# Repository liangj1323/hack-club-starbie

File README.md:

This is the repo for my hack club half life week one project for the Starbie PCB
It is an idea like a desk-pet Starboy, which you can shake, etc with it and it reacts
This is my first hack club project AND my first PCB and big project, I have no experience in PCBs or designing microcontrollers or other boards so for my first attempt, even though I finished with a list of errors on my PCB, I think I have learnt quite a lot and I have tried my best

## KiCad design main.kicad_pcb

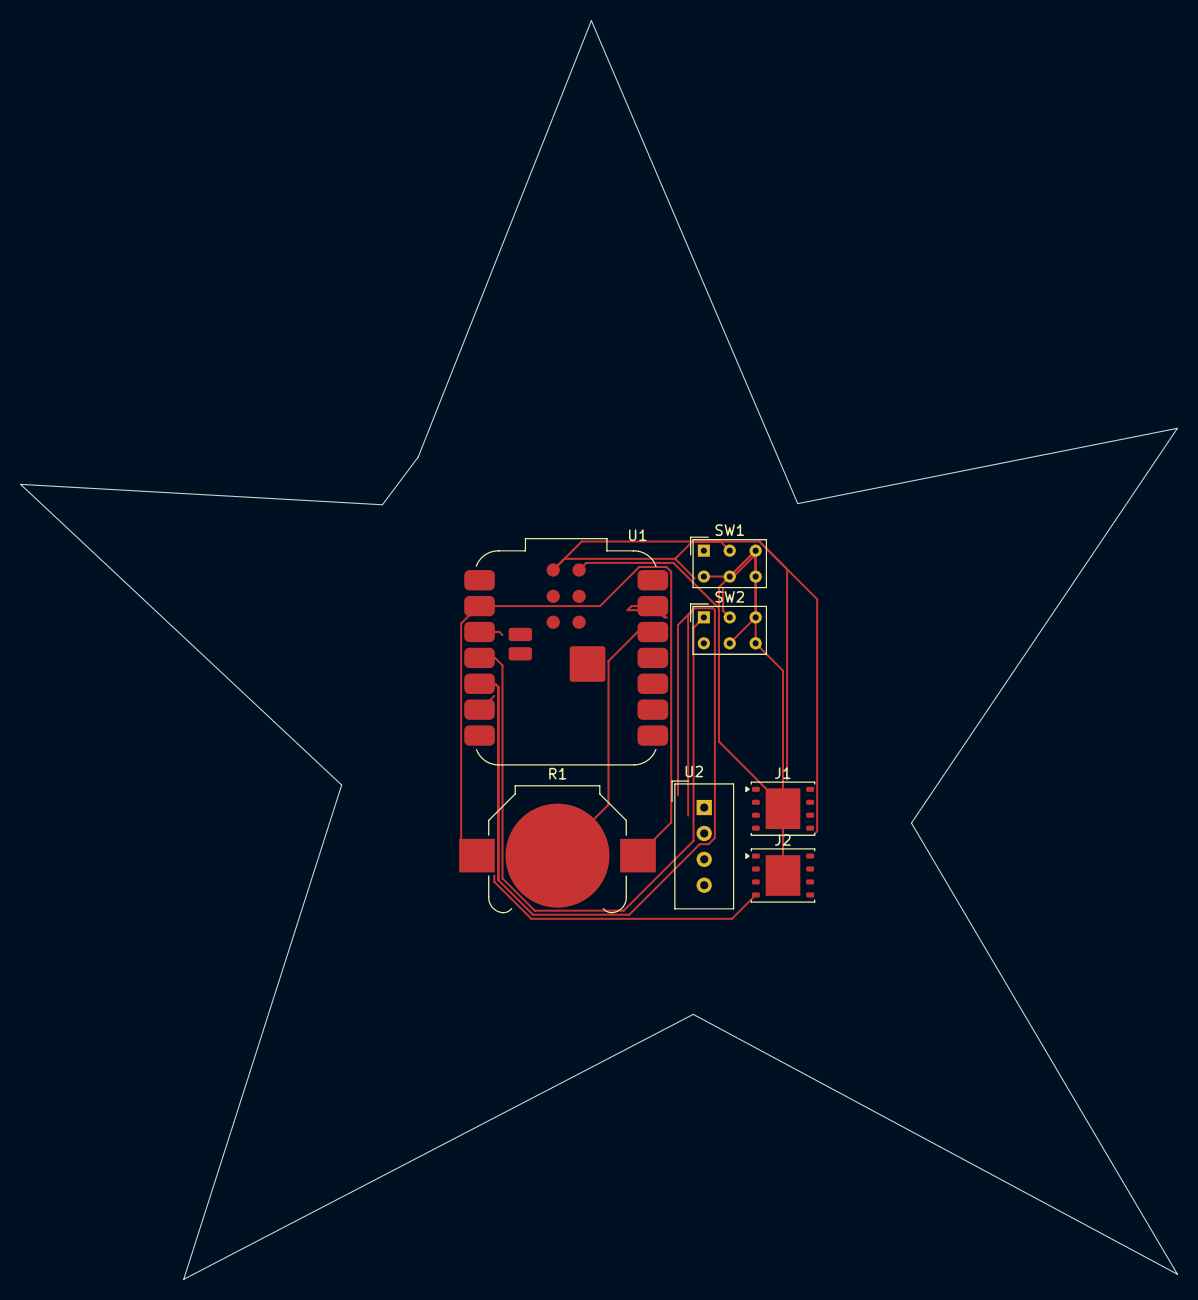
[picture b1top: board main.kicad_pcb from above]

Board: 2 copper layers, 113.5 x 123.5 mm, 7 parts (0 on the bottom side), 7 nets.

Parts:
J1: Conn_01x04_Pin; WSON-8-1EP_6x5mm_P1.27mm_EP3.4x4mm
J2: Conn_01x08_Pin; WSON-8-1EP_6x5mm_P1.27mm_EP3.4x4mm
R1: 10k; BatteryHolder_Keystone_3000_1x12mm
SW1, SW2: SW_Push; SW_NKK_GW12LJP
U1: XIAO-ESP32-C3-SMD; MCU_Seeed_ESP32C3
U2: DHT11; Aosong_DHT11_5.5x12.0_P2.54mm

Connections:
+3.3V: J1.2, J2.1, R1.2, U1.12 (3V3_OUT), U2.1 (VDD)
/DHT11 DATA: R1.1, U1.2 (D1), U2.2 (DATA)
/GP102: SW1.1, U1.3 (D2)
/GP103: SW2.1, U1.4 (D3)
/SCL: J1.3, J2.3, U1.5 (D4)
/SDA: J1.4, J2.4, U1.6 (D5)
GND: J1.1, J2.2, SW1.2, SW2.2, U1.13 (GND), U1.18 (GND), U2.4 (GND)
